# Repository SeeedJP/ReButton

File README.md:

ReButton is now available at [Seeed Bazaar](https://www.seeedstudio.com/ReButton-p-2930.html).

[日本語版ドキュメント](README-ja.md)

[HoL document in Simplified Chinese](IoTinAction_Hands-on%20Lab_ReButton%20OTA%20CN.pdf)

[!WARNING]
**Warning (Updated March 7, 2023)**

Due to the migration of the root certificate for Azure IoT Hub/Azure IoT Hub Device Provisioning Service planned from February 15, 2023 to February 15, 2024 [1], it is necessary to update ReButton's firmware to **v1.12 or later** [2].

Note that **OTA updates will fail** for firmware v1.0 to 1.11, so [firmware updates via SWD](#swd-serial-wire-debug) must be performed.

##### What is happening?
Between February 15, 2023 and February 15, 2024, the root certificate of the server certificate for Azure IoT Hub/Azure IoT Hub Device Provisioning Service will be gradually changed.

* Azure IoT Hub: February 15, 2023 to October 15, 2023
* Azure IoT Hub Device Provisioning Service: January 15, 2024 to February 15, 2024

##### What happens if I don't update the firmware?
After February 15, 2023, there is a possibility that ReButton will no longer be able to connect to Azure IoT Hub/IoT Central.

---
1. See "[Azure IoT TLS: Critical changes are almost here! (…and why you should care)](https://techcommunity.microsoft.com/t5/internet-of-things-blog/azure-iot-tls-critical-changes-are-almost-here-and-why-you/ba-p/2393169)" for more details.
2. Factory default firmware is "v1.0".
[!ENDWARNING]

# Overview

**Build IoT solutions with IoT Button!**

Seeed ReButton is a developer device for simple trigger actions, supporting multiple clicks and long press.
In addition, you can connect Seeed Grove sensors to add more data points.

1. When you push ReButton, it will power up and connect to Internet via pre-configured Wi-Fi.
2. ReButton will receive Device Twin changes from pre-configured Azure IoT Central or Azure IoT Hub.
3. ReButton will send Device to Cloud Message to pre-configured Azure IoT Central or Azure IoT Hub.
4. After D2C message is sent, ReButton will shutdown.

# Key Features

## Multiple Trigger Support

* Single click
* Double click
* Triple click
* Long press (>3sec.)
* Super long press (>6sec.)

## Seeed Grove Sensor Support

Connect I2C or GPIO Grove sensors to the bottom of ReButton.
```
NOTE:
Software development/update is required.
```

## Cloud Support

Supports Azure IoT Central and Azure IoT Hub.

## OTA Support

You can update ReButton firmware over-the-air.

## Low Energy Design

ReButton runs with 2x AAA Alkaline battery.

# Quickstarts

## 1. Getting access to ReButton

Use AP Mode (Access Point Mode) to configure ReButton. **To avoid battery drain, ReButton will automatically shutdown in 10 minutes, at AP mode. So that we recommend you to setup IoT Hub or IoT Central, first.**

**AP Mode consume power. Please use fresh battery to start using ReButton.**

1. Hold button until RGB LED turns into White.
  RGB LED will start with Blue, Yellow, Cyan, then White. This will take about 10 seconds.

1. Release button and confirm ReButton is in AP mode.
  When ReButton successfully boots into AP Mode, RGB LED will blink in White.

1. Connect to AP
  Look for Wi-Fi Access Point `AZB-xxxxxxxxxxxx` and connect to it from your PC.
  (`xxxxxxxxxxxx` is MAC address of your ReButton Wi-Fi.)

4. Use a Web Browser to access ReButton - Home at `http://192.168.0.1`.

## 2. Wi-Fi Configuration

Configure Wi-Fi settings to connect to Internet.

1. Click `Wi-Fi` at ReButton - Home.

2. Select your Wi-Fi Access Point from `Wi-Fi SSID` list.
  If you do not see your Access Point, refresh browser.
1. Enter `Wi-Fi Passphrase` for your Wi-Fi AP.
1. In case you would like to use specific Internet Time Server, enter FQDN to `Time Server`.
  _Default Internet Time Server is pool.ntp.org -> cn.pool.ntp.org -> europe.pool.ntp.org -> asia.pool.ntp.org -> oceania.pool.ntp.org ._

1. Click `Save`.

## 3. Cloud Configuration

### 3-1. Azure IoT Hub

**NOTE: Skip to next section if you would like to connct to Azure IoT Central.**

In order to send Device to Cloud (D2C) message to Azure IoT Hub, save Connection String in ReButton.

**To get the connection string, [This](IoT_Hub.md) page could be helpful.**

1. Browse to ReButton - Home page then click `Azure IoT Hub`.
1. Paste Connection String to `Azure IoT Hub connection string`.
1. Click `Save`.

### 3-2. Azure IoT Central

**NOTE: Skip this section if you already configured IoT Hub at section 3-1.**

In order to send Device to Cloud (D2C) message to Azure IoT Central, save device provisioning information in ReButton.

In order to connect ReButton to Azure IoT Central, the device template for ReButton needs to be defined in you Azure IoT Central Application. _Please refer [Azure IoT Central Document](https://docs.microsoft.com/en-us/azure/iot-central/howto-set-up-template) for more information._

1. Create a device template for ReButton in Azure IoT Central.

|Display name|Name|Capability type|Semantic type|Schema|Unit|
|:--|:--|:--|:--|:--|:--|
|Battery Voltage|batteryVoltage|Telemetry|Voltage|Double|Volt|
|Message|message|Telemetry|Event|String||
|Action Number|actionNum|Telemetry|Event|String||

- Battery Voltage

- Message

- Action Number

2. Create a device in Azure IoT Central.

3. Click `Connect` on Top Right corner of Azure IoT Central page.

4. Copy 3 values.
    1. `Scope ID`
    1. `Device ID`
    1. `Primary Key`

5. Browse to ReButton - Home page then click `Azure IoT Central`.
1. Enter `Scope ID`, `Device ID`, `SAS Key` from Azure IoT Central.
1. Click `Save`.

## 4. Power off

Exit AP Mode and power off ReButton.

1. Click `Shutdown` button.

# Other informations
## Device To Cloud (D2C) Messsage

Button push will trigger D2C message to the cloud.
ReButton supports 5 types of button triggers and default D2C message strings are following.

|Clicks|RGB led|actionNum|message|
|:--|:--|:--|:--|
|Single click|Blue|1|"Single click"|
|Double click|Lime|2|"Double click"|
|Triple click|Magenta|3|"Triple click"|
|Long press (> 3sec.)|Yellow|10|"Long press"|
|Super long press (> 6sec.)|Cyan|11|"Super long press"|

Examples of D2C message:
```json
{
  "actionNum": "1",
  "message": "Single click",
  "batteryVoltage": 2.59
}

{
  "actionNum": "2",
  "message": "Double click",
  "batteryVoltage": 2.59
}

{
  "actionNum": "3",
  "message": "Triple click",
  "batteryVoltage": 2.59
}

{
  "actionNum": "10",
  "message": "Long press",
  "batteryVoltage": 2.59
}

{
  "actionNum": "11",
  "message": "Super long press",
  "batteryVoltage": 2.59
}
```

# Firmware Development
## Development environment
Please download and install [Arduino IDE](https://www.arduino.cc/en/Main/Software), not web editor.

On the preferenceof Arduino IDE, enter `https://www.seeed.co.jp/package_SeeedJP_index.json` to "Additional Boards Manager URLs".

Then goes to the Boards Manager from Tools > Board. And search ReButton board package by entering "rebutton". Then choose the candidate and click the "install" button.

After the install process ( it may take a few minutes ) you can choose "ReButton" through Tool -> Board on Arduino IDE.

## Firmware sample code
The source code is:
* [ReButton App](https://github.com/SeeedJP/ReButtonApp)

## Firmware OTA Update
ReButton supports Firmware OTA.
Browse to `Firmware Update` page to see the current vesrion of firmware and update to new firmware.

#### Current Firmware Version
Browse to ReButton - Home then click `Firmware Update` to see current firmware version of ReButton.

#### How to update firmware through OTA
For OTA firmware update process, please refer [this](OTA.md) page.

## SWD (Serial Wire Debug)

ReButton has SWD pads for MCU development. **Please do this on your own risk,**  it is easy to make your ReButton brick.
Following picture show the SWD signals of the PAD. You can connect this PADs to debug adapters by using [TC2030-CTX 6-Pin Cable](http://www.tag-connect.com/TC2030-CTX) or solder directly to the PADs.

We are preparing for providing software development informations and affordable debug adapter. For your recovering purpose, you can download ReButton default firmware binary 'ReButton.1.0_with_bootloader.bin' from [here](https://github.com/SeeedJP/ReButton/tree/master/firmware). You need to flash this binary for target `STM32F412RG` and flash address `0x0800 0000` since this default firmware binary includes bootloader.

1. Connect the debug adapter to ReButton's SWD pads.
2. Install batteries.
3. **While holding (physical) button of ReButton**, execute download.

example:
```
openocd -f /usr/local/share/openocd/scripts/interface/cmsis-dap.cfg -c 'transport select swd' -f /usr/local/share/openocd/scripts/target/stm32f4x.cfg -c "program ReButton.1.0_with_bootloader.bin verify reset exit 0x08000000"
```

When you flash a binary without bootloader (such as `ReButtonApp.1.x.bin`), you should flash address `0x0800 C000`.

# Specification

## Hardware

|Description|Value|
|:--|:--|
|MCU module|MXCHIP EMW3166|
|Input|1x Push button|
|Output|1x RGB led|
|Extension|1x I2C Grove connector (3.3V I/O)|
|Extras|1x Jumper switch|
||1x SWD pads|
||1x UART for debugging|
|Power supply|2x AAA Alkaline batteries (LR03)|
|Internal supply voltage|3.3V|
|Dimension|70mm\*70mm\*25mm|

## Design files
* [Schematics](https://github.com/SeeedJP/ReButton/tree/master/electronics)
* [Housing](https://github.com/SeeedJP/ReButton/tree/master/mechanicals)

These files are licensed under [CC-BY-SA](https://creativecommons.org/licenses/by-sa/4.0/deed.en).

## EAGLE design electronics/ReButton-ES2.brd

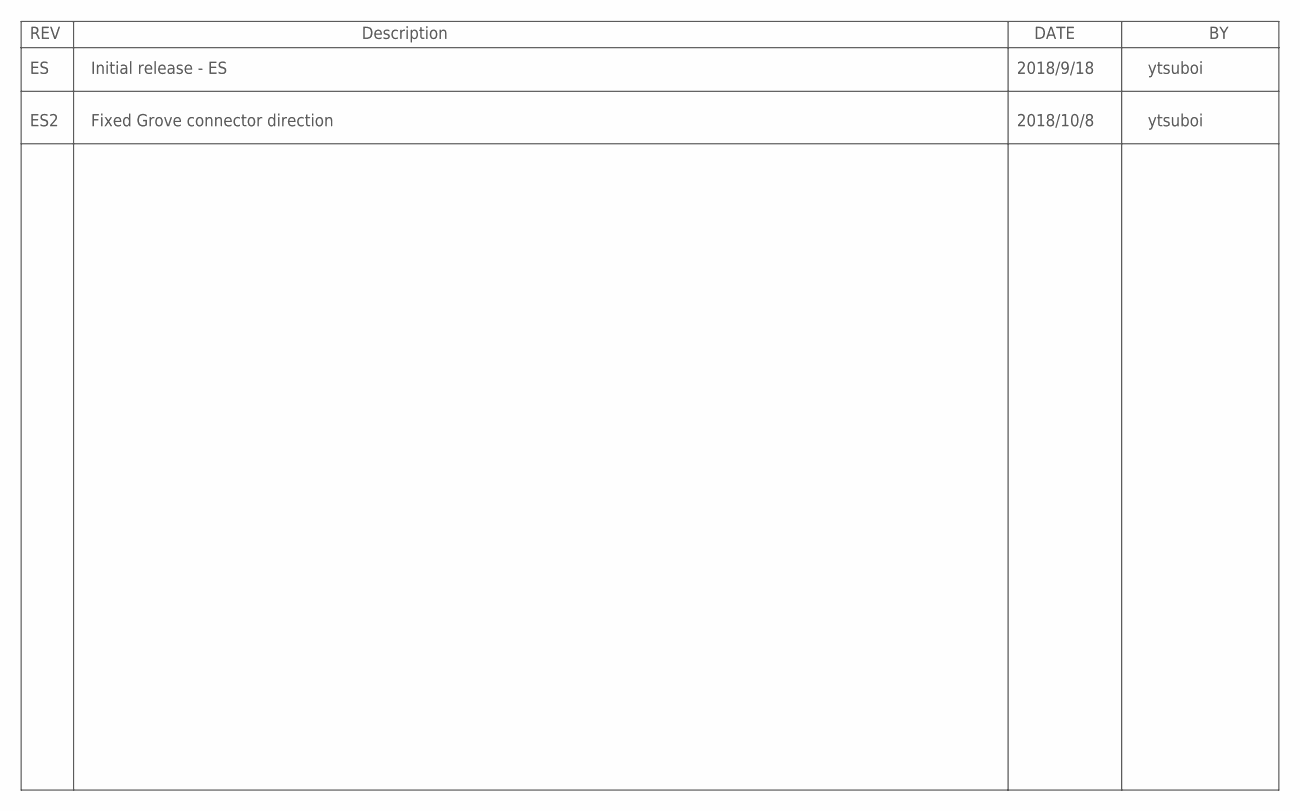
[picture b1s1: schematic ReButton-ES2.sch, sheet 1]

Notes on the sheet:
Initial release - ES
2018/9/18
ytsuboi
Fixed Grove connector direction
ES2
2018/10/8

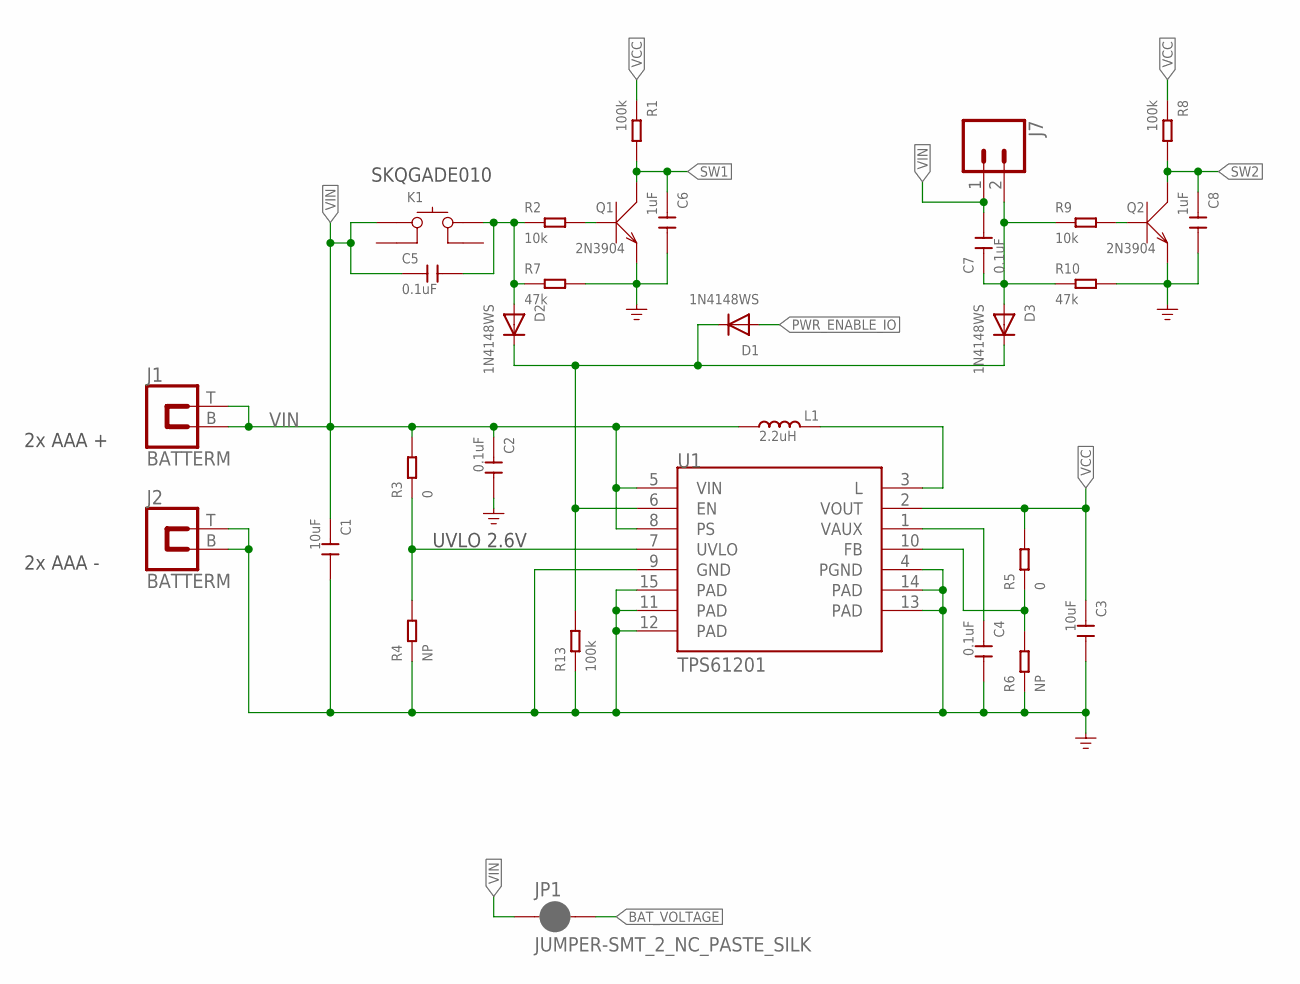
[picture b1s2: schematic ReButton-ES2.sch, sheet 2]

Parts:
C1, C3: 10uF; C0805
C2, C4, C5, C7: 0.1uF; C0402
C6, C8: 1uF; C0402
D1, D2, D3: 1N4148WS; SOD-323
J1, J2: BATTERM
J7: CONN_02LOCK; 1X02_LOCK
JP1: JUMPER-SMT_2_NC_PASTE_SILK; SMT-JUMPER_2_NC_PASTE_SILK
K1: BUTTON-4P-6.2X6.2; SW4-SMD-6.2X6.2MM
L1: 2.2uH; L3030-TAIYO-YUDEN-NR3012
Q1, Q2: 2N3904; SOT-23
R1, R8, R13: 100k; R0402
R2, R9: 10k; R0402
R3, R5: 0; R0402
R4, R6: NP; R0402
R7, R10: 47k; R0402
U1: TPS61201; QFN-10_PAD

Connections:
BAT_VOLTAGE: JP1.2; also elsewhere on the board
FB: R5.1, R6.2, U1.10 (FB)
GND: C1.2, C2.2, C3.2, C4.2, C6.2, C8.2, J2.B, J2.T, Q1.2 (E), Q2.2 (E), R4.1, R6.1, R7.2, R10.2, R13.1, U1.4 (PGND), U1.9 (GND), U1.11 (PAD), U1.12 (PAD), U1.13 (PAD), U1.14 (PAD), U1.15 (PAD); also elsewhere on the board
unnamed: C4.1, U1.1 (VAUX)
unnamed: L1.2, U1.3 (L)
unnamed: D1.C, D2.C, D3.C, R13.2, U1.6 (EN)
unnamed: Q1.1 (B), R2.2
unnamed: C5.2, D2.A, K1.2 (B0), R2.1, R7.1
unnamed: C7.1, D3.A, J7.2, R9.1, R10.1
unnamed: Q2.1 (B), R9.2
PWR_ENABLE_IO: D1.A; also elsewhere on the board
SW1: C6.1, Q1.3 (C), R1.2; also elsewhere on the board
SW2: C8.1, Q2.3 (C), R8.2; also elsewhere on the board
UVLO: R3.1, R4.2, U1.7 (UVLO)
VCC: C3.1, R1.1, R5.2, R8.1, U1.2 (VOUT); also elsewhere on the board
VIN: C1.1, C2.1, C5.1, C7.2, J1.B, J1.T, J7.1, JP1.1, K1.1 (A0), L1.1, R3.2, U1.5 (VIN), U1.8 (PS)

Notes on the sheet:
UVLO 2.6V
2x AAA +
2x AAA -
SKQGADE010

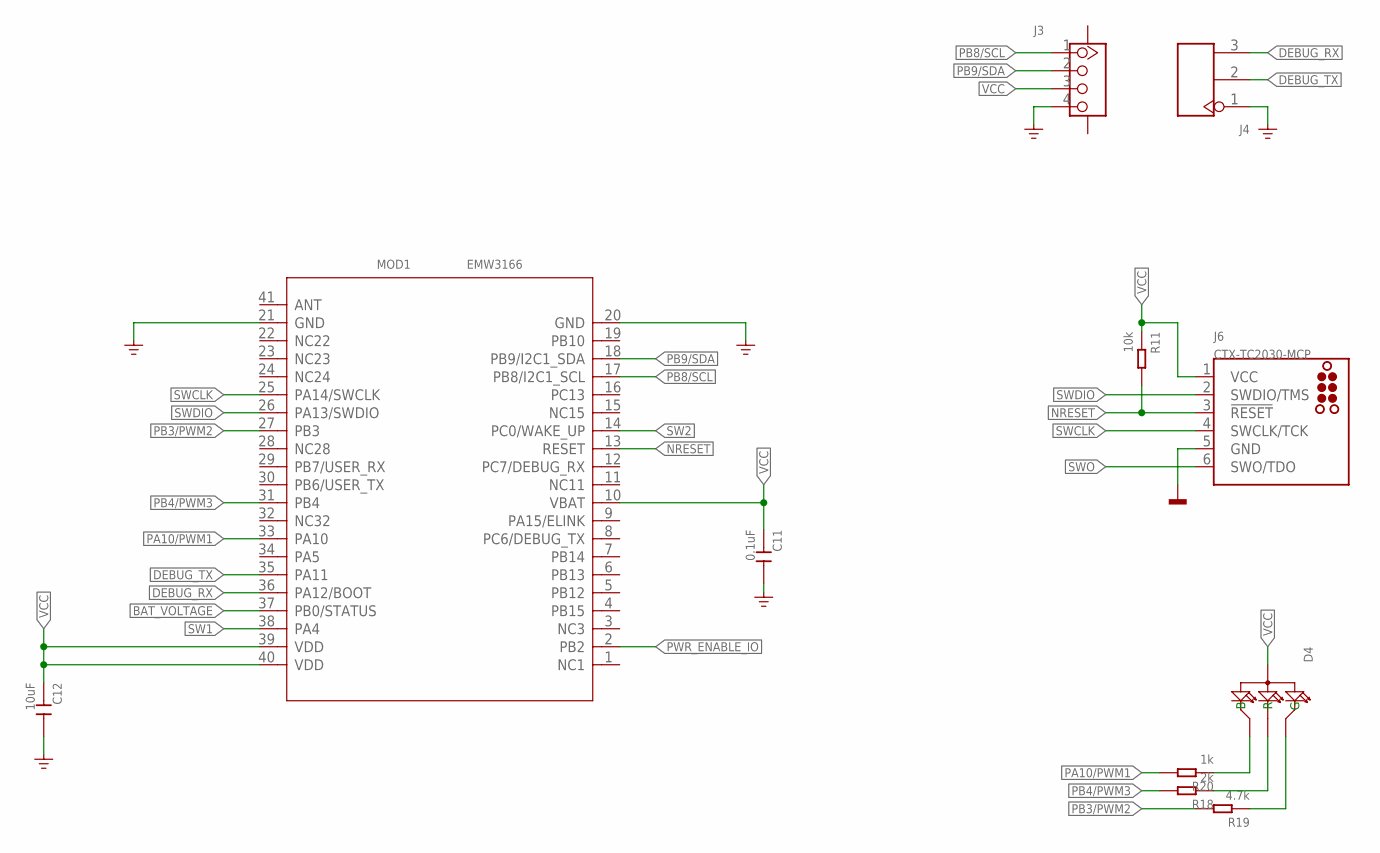
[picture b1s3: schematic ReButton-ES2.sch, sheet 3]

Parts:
C11: 0.1uF; C0402
C12: 10uF; C0805
D4: LED-ARGB-4P-19-237; LED4-1.6X1.6X0.35MM
J3: GROVE-CONNECTOR-SMD'DD'; HW4-SMD-2.0
J4: HEADER-3P; H3-2.3-65/35MIL
J6: CTX-TC2030-MCP; TC2030-MCP
MOD1: EMW3166; MODULE-WIFI-EMW3166
R11: 10k; R0402
R18: 2k; R0402
R19: 4.7k; R0402
R20: 1k; R0402

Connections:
BAT_VOLTAGE: MOD1.37 (PB0/STATUS); also elsewhere on the board
DEBUG_RX: J4.3, MOD1.36 (PA12/BOOT)
DEBUG_TX: J4.2, MOD1.35 (PA11)
GND: C11.2, C12.2, J3.4, J4.1, J6.5 (GND), MOD1.20 (GND), MOD1.21 (GND); also elsewhere on the board
unnamed: D4.4 (R), R18.1
unnamed: D4.2 (G), R19.1
unnamed: D4.1 (B), R20.1
NRESET: J6.3 (!RESET!), MOD1.13 (RESET), R11.2
PA10/PWM1: MOD1.33 (PA10), R20.2
PB3/PWM2: MOD1.27 (PB3), R19.2
PB4/PWM3: MOD1.31 (PB4), R18.2
PB8/SCL: J3.1, MOD1.17 (PB8/I2C1_SCL)
PB9/SDA: J3.2, MOD1.18 (PB9/I2C1_SDA)
PWR_ENABLE_IO: MOD1.2 (PB2); also elsewhere on the board
SW1: MOD1.38 (PA4); also elsewhere on the board
SW2: MOD1.14 (PC0/WAKE_UP); also elsewhere on the board
SWCLK: J6.4 (SWCLK/TCK), MOD1.25 (PA14/SWCLK)
SWDIO: J6.2 (SWDIO/TMS), MOD1.26 (PA13/SWDIO)
SWO: J6.6 (SWO/TDO)
VCC: C11.1, C12.1, D4.3 (+), J3.3, J6.1 (VCC), MOD1.10 (VBAT), MOD1.39 (VDD), MOD1.40 (VDD), R11.1; also elsewhere on the board

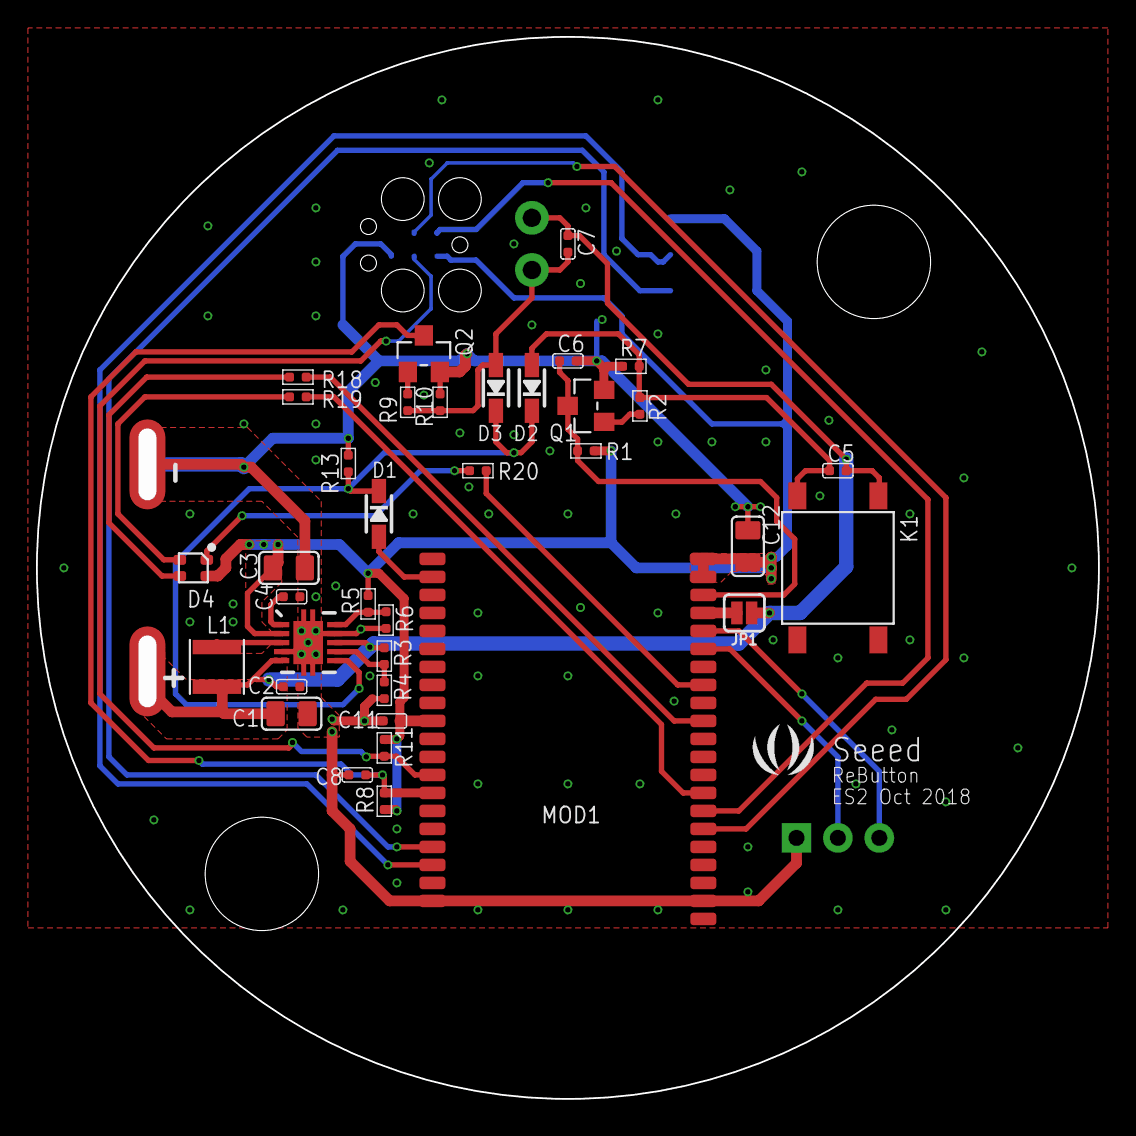
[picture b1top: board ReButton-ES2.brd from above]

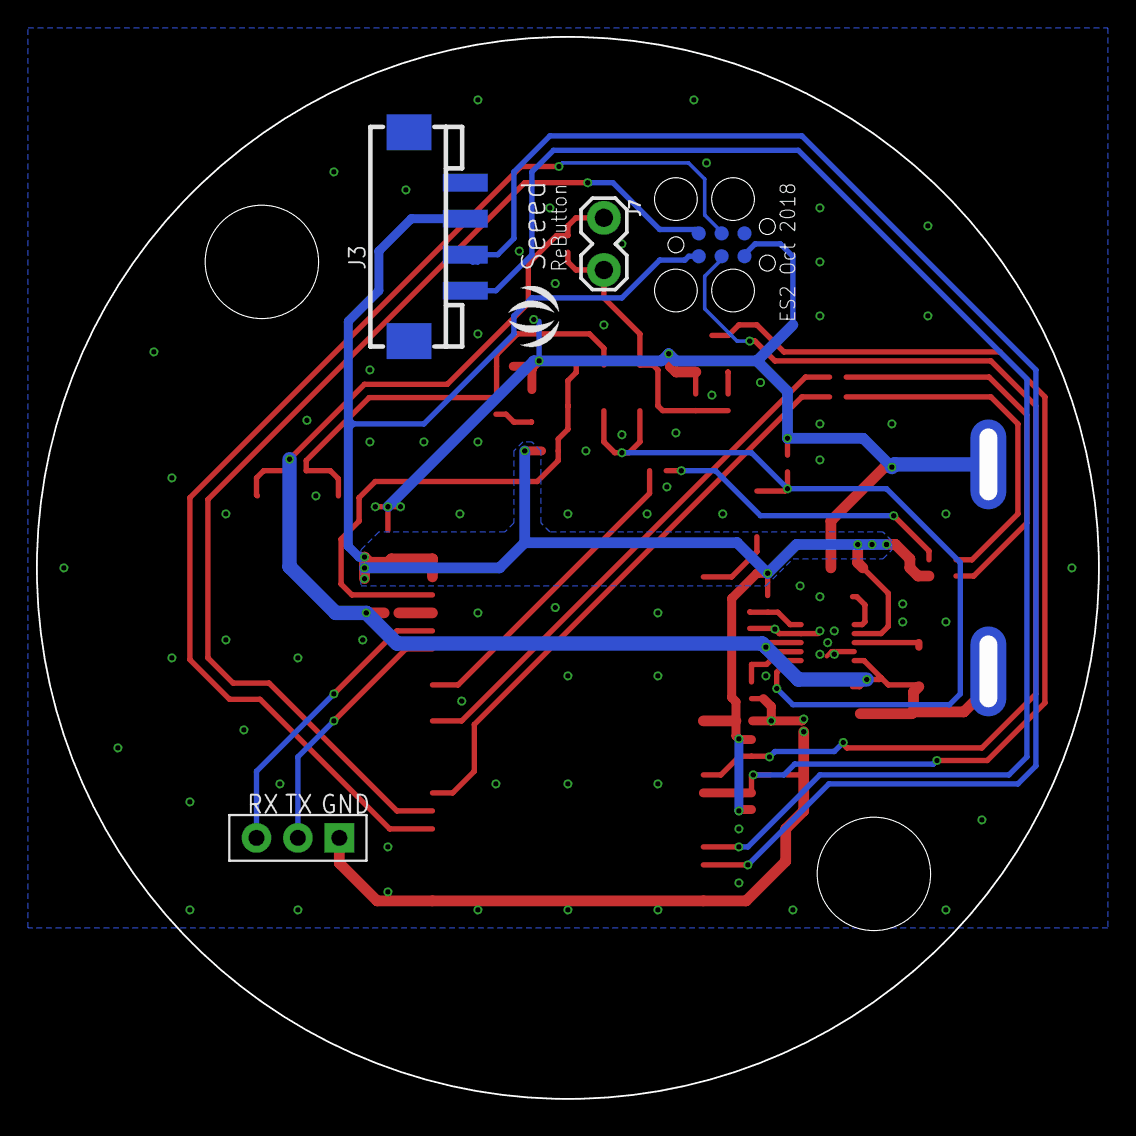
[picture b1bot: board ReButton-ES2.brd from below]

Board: 2 copper layers, 58.1 x 58.1 mm, 44 parts (5 on the bottom side), 29 nets.

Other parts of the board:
U$9, U$15: SEEED-SILK--TNAME-160*153MIL

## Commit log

2018-10-15 1st commit
2018-10-15 Set theme jekyll-theme-slate
2018-10-16 added google analytics
2018-10-28 added IoT Hub getting started and fixed some minor issues
2018-10-28 added about Azure CLI and Azure IoT extension
2018-10-29 added how to find IoT Hub
2018-10-29 Review 1
2018-10-29 One more
2018-10-29 fixed blockquote
2018-10-29 fixed description about free fier
2018-12-07 Add generatecrc tool.
2018-12-07 added generatecrc desc
2018-12-07 adding firmware dev env and sourcecode link
2018-12-09 adding OTA description
2018-12-09 add hints to OTA.md
2018-12-13 adding HoL Chinese document
2019-01-08 Add ReButtonApp 1.0, 1.1
2019-01-08 Add readme.md
2019-01-20 Add firmware
2019-04-12 Update README.md
    Added link to Bazaar page. Fixed link to Hands on Lab document.
2019-04-25 Change board manager url
2019-05-29 Image of Japanese version
2019-05-30 added japanese documents
2019-05-31 Japanese document release
    Added link to Japanese version.
    Fixed typo.
    Added note to recommend using fresh battery,
2019-05-31 fixing the table
2019-08-07 add firmware's link
2021-06-07 Updated tables and images for current IoT Central
2021-06-07 Minor fix
    - separate bullets and images
    - removed trailing white space
2021-06-07 Change border color
2021-07-08 Added DTDL model file
2023-02-27 Update README-ja.md (#17)
    * Update README-ja.md
    * Update README
2023-03-06 Change to internal link
2023-03-07 Changed to replace specific strings at build time
    The target string is below.
    [!WARNING], [!ENDWARNING]
    expressing warning
    [!NOTE], [!ENDNOTE]
    expressing note
2023-03-07 added notice regarding the Azure IoT services root certificate change
2023-03-12 Add firmware ReButton.1.12_with_bootloader.bin
    Created by following step:
    $ cp .../ReButtonArduinoPlatform/AZ3166/src/bootloader/boot.bin .
    $ dd if=/dev/zero bs=1k count=48 | tr "\000" "\377" > ReButton.1.12_with_bootloader.bin
    $ dd if=./boot.bin of=ReButton.1.12_with_bootloader.bin conv=notrunc
    $ cat ./ReButtonApp.1.12.bin >> ReButton.1.12_with_bootloader.bin
2023-03-14 Add firmware ReButton.1.12_with_bootloader.bin (#19)
    Created by following step:
    $ cp .../ReButtonArduinoPlatform/AZ3166/src/bootloader/boot.bin .
    $ dd if=/dev/zero bs=1k count=48 | tr "\000" "\377" > ReButton.1.12_with_bootloader.bin
    $ dd if=./boot.bin of=ReButton.1.12_with_bootloader.bin conv=notrunc
    $ cat ./ReButtonApp.1.12.bin >> ReButton.1.12_with_bootloader.bin

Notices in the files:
parts and their libraries:
microbuilder: This work is placed in the public domain, and may be freely used for commercial and non-commercial work with the following conditions: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
tag-connect: ©2009 ROFA.cz - modified and updated by Robert Darlington ‹rdarlington@gmail.com›
